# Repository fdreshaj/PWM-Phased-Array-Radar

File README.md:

# PWM Phased Array Radar
PWM Phased Array Radar Project

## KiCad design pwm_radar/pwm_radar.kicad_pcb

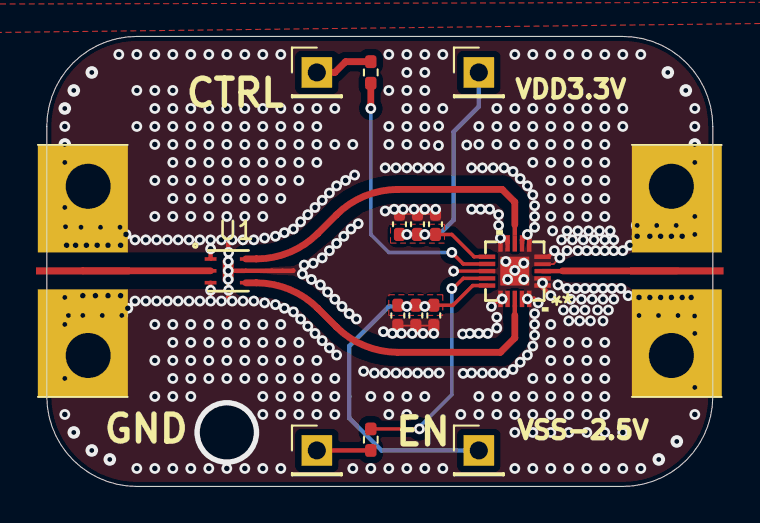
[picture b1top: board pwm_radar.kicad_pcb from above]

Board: 4 copper layers, 37.0 x 25.0 mm, 16 parts (0 on the bottom side), 11 nets.

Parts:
C1, C4: 10u; C_0402_1005Metric_Pad0.74x0.62mm_HandSolder
C2, C3, C6: 100p; C_0402_1005Metric_Pad0.74x0.62mm_HandSolder
C5: 100n; C_0402_1005Metric_Pad0.74x0.62mm_HandSolder
J1, J6: Conn_Coaxial; Wurth_RF_PWM_Conn
J2, J3, J7, J8: Conn_01x01_Pin; PinHeader_1x01_P2.54mm_Vertical
R1, R2: 0; R_0402_1005Metric_Pad0.72x0.64mm_HandSolder
U1: MC1630-1_MNC
U2: ADRF5020BCCZN

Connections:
CTRL: R1.1, U2.12 (CTRL)
EN: R2.1, U2.14 (EN)
GND: C1.2, C2.2, C3.2, C4.2, C5.2, C6.2, J1.2 (Ext), J6.2 (Ext), U1.1 (GND), U1.3 (GND), U1.5 (NC), U1.7 (GND_PAD), U2.1 (GND), U2.2 (GND), U2.4 (GND), U2.5 (GND), U2.6 (GND), U2.7 (GND), U2.9 (GND), U2.10 (GND), U2.13 (GND), U2.16 (GND), U2.17 (GND), U2.19 (GND), U2.20 (GND), U2.21
unnamed: J1.1 (In), U1.2 (Primary)
unnamed: J2.1, R1.2
unnamed: J6.1 (In), U2.3 (RFC)
unnamed: J7.1, R2.2
RF1+: U1.6 (Secondary_Dot), U2.8 (RF1)
RF1-: U1.4 (Secondary), U2.18 (RF2)
VDD: C1.1, C2.1, C3.1, J3.1, U2.11 (VDD)
VSS: C4.1, C5.1, C6.1, J8.1, U2.15 (VSS)

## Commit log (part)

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2026-06-03 Inital Sch and Lay
    Inital Sch and Lay
    Need to find 50 ohm for Rodgers
2026-06-03 added 50 ohm lines
2026-06-03 minor changes
    minor changes
2026-06-09 pcb files changes
    pcb changes
2026-06-09 more changes
    more changes and vivaldi
2026-06-10 changes
    changes
2026-06-22 pcb changes
    pcb changes
2026-06-24 vivaldi antenna put in
    vivaldi antenna put in
2026-06-24 added ant
    added antenna
2026-06-25 added vivaldi antenna
    added vivaldi antenna
2026-06-25 fixing some final touches
2026-06-25 fixed some issues
    fixed issues
2026-06-25 final_checking
    final_checking
2026-06-25 gerbers
    gerbers
2026-06-25 new
    new
2026-06-26 final gerbs v1
    final gerbs v1
